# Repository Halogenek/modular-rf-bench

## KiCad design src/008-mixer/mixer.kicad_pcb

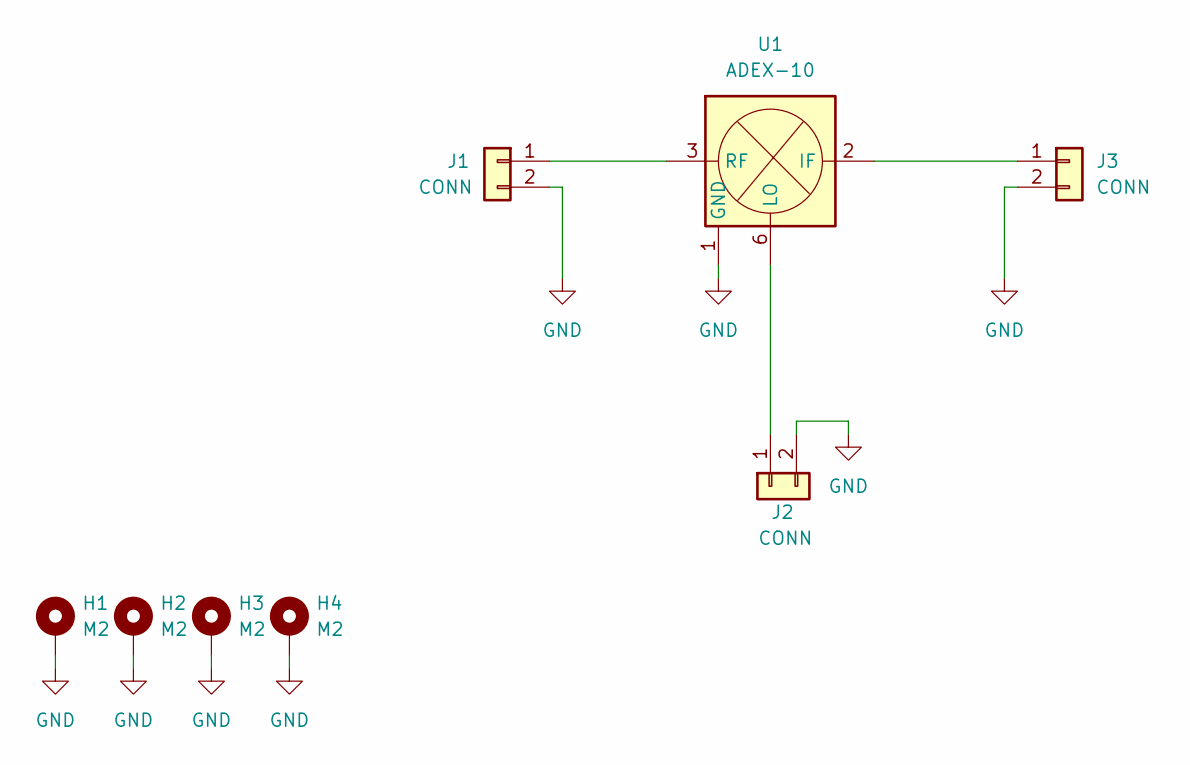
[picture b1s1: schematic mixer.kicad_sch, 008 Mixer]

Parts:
H1, H2, H3, H4: M2; M2-hole
J1, J2, J3: CONN; edge-connector
U1: ADEX-10; Mini-Circuits_CD542_LandPatternPL-052

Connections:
GND: H1.1, H2.1, H3.1, H4.1, J1.2, J2.2, J3.2, U1.1 (GND), U1.4 (GND), U1.5 (GND)
unnamed: J1.1, U1.3 (RF)
unnamed: J2.1, U1.6 (LO)
unnamed: J3.1, U1.2 (IF)

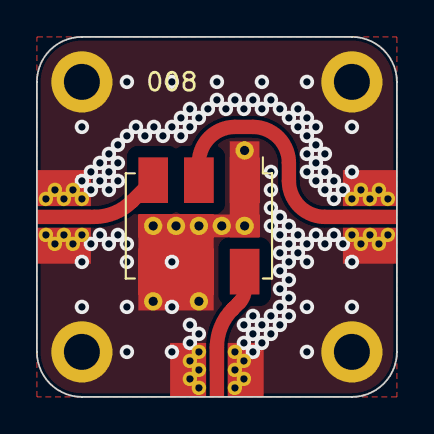
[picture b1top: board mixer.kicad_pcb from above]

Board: 2 copper layers, 20.0 x 20.0 mm, 8 parts (0 on the bottom side), 4 nets.

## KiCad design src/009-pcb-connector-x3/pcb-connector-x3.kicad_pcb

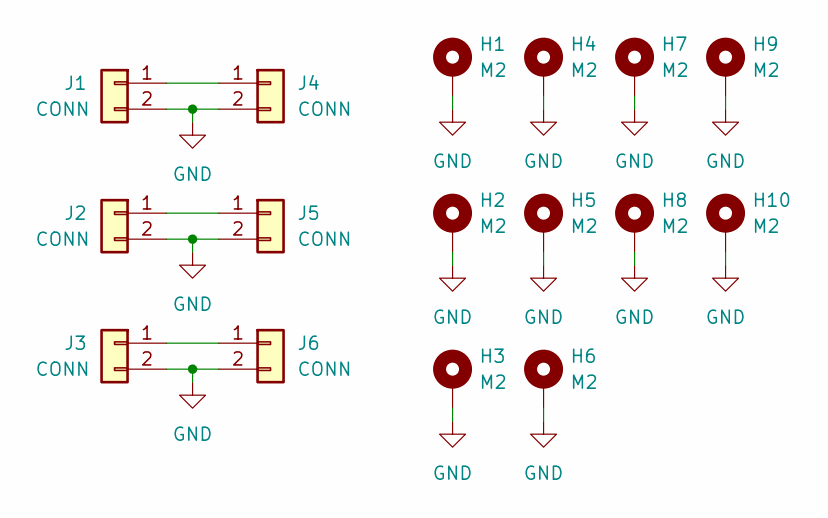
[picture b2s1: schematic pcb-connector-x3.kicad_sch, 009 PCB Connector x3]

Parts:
H1, H2, H3, H4, H5, H6, H7, H8, H9, H10: M2; M2-hole
J1, J2, J3, J4, J5, J6: CONN; edge-connector

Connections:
GND: H1.1, H2.1, H3.1, H4.1, H5.1, H6.1, H7.1, H8.1, H9.1, H10.1, J1.2, J2.2, J3.2, J4.2, J5.2, J6.2
unnamed: J1.1, J4.1
unnamed: J2.1, J5.1
unnamed: J3.1, J6.1

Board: 2 copper layers, 16 parts (0 on the bottom side), 4 nets, no tracks yet.

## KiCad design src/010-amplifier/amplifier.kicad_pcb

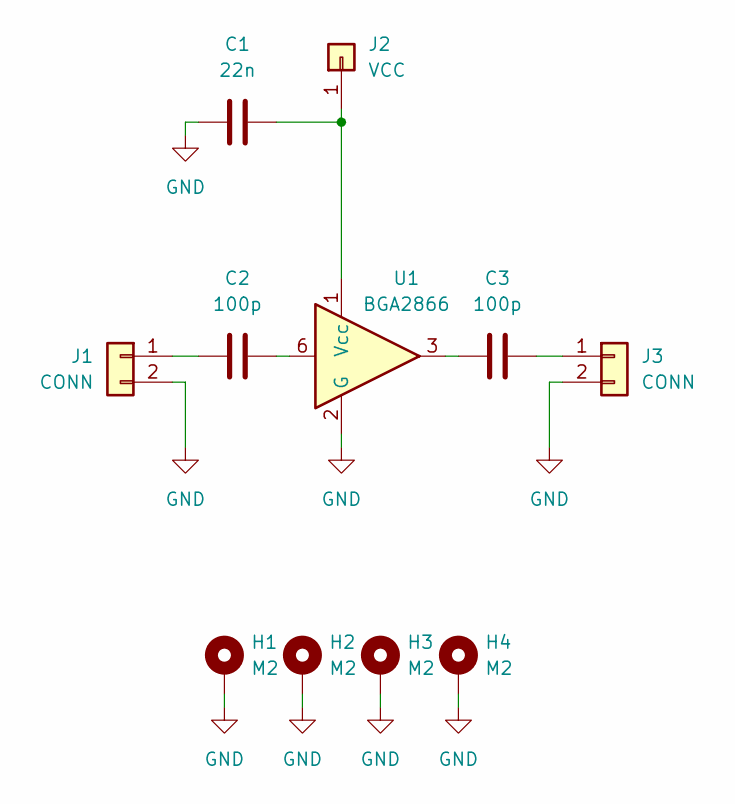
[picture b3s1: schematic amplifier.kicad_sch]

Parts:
C1: 22n; C_0603_1608Metric
C2, C3: 100p; C_0603_1608Metric
H1, H2, H3, H4: M2; M2-hole
J1, J3: CONN; edge-connector
J2: VCC; SolderWire-0.25sqmm_1x01_D0.65mm_OD1.7mm
U1: BGA2866; SOT-363_SC-70-6

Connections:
GND: C1.1, H1.1, H2.1, H3.1, H4.1, J1.2, J3.2, U1.2 (G), U1.4 (G), U1.5 (G)
unnamed: C1.2, J2.1, U1.1 (Vcc)
unnamed: C2.1, J1.1
unnamed: C2.2, U1.6
unnamed: C3.1, U1.3
unnamed: C3.2, J3.1

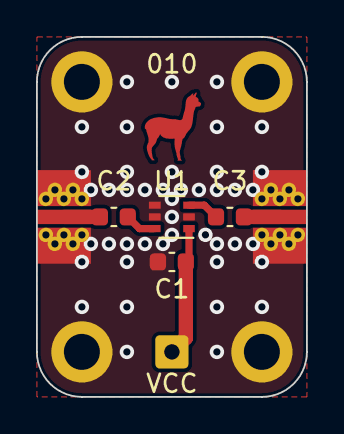
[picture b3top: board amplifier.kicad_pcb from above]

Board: 2 copper layers, 15.0 x 20.0 mm, 11 parts (0 on the bottom side), 6 nets.

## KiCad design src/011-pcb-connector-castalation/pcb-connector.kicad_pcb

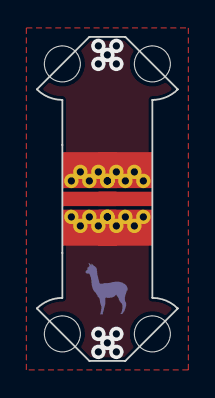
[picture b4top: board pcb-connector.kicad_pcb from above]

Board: 2 copper layers, 7.8 x 18.0 mm, 6 parts (0 on the bottom side), 2 nets, no tracks yet.

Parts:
H1, H2, H3, H4: M2; M2-hole
J1, J2: CONN; edge-connector

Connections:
GND: J1.2, J2.2
unnamed: J1.1, J2.1

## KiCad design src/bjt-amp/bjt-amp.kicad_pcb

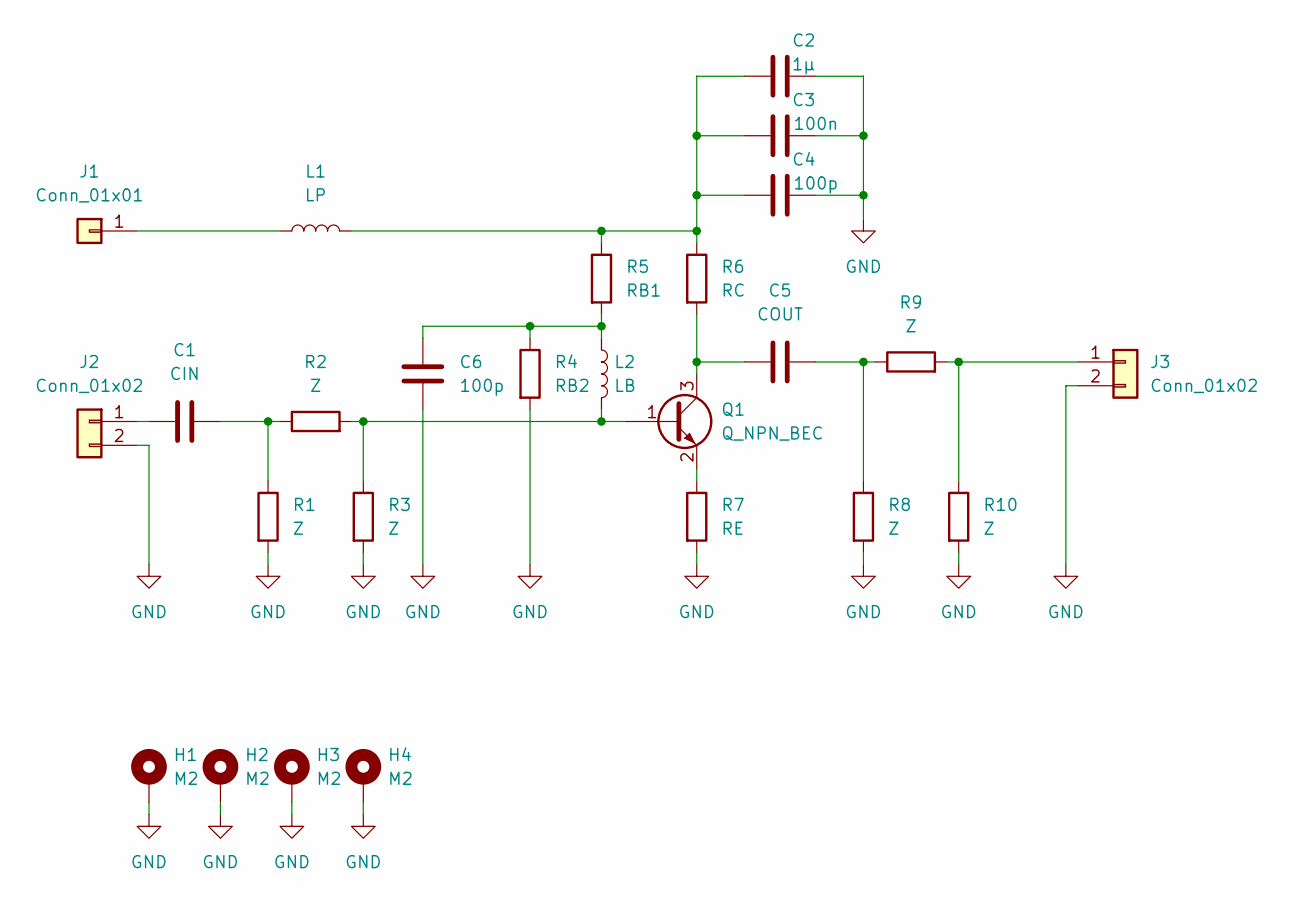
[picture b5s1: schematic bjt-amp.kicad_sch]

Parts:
C1: CIN; C_0603_1608Metric
C2: 1µ; C_0603_1608Metric
C3: 100n; C_0603_1608Metric
C4, C6: 100p; C_0603_1608Metric
C5: COUT; C_0603_1608Metric
H1, H2, H3, H4: M2; M2-hole
J1: Conn_01x01; SolderWire-0.25sqmm_1x01_D0.65mm_OD1.7mm
J2, J3: Conn_01x02; edge-connector
L1: LP; L_0603_1608Metric
L2: LB; L_0603_1608Metric
Q1: Q_NPN_BEC; SOT-23
R1, R2, R3, R8, R9, R10: Z; R_0603_1608Metric
R4: RB2; R_0603_1608Metric
R5: RB1; R_0603_1608Metric
R6: RC; R_0603_1608Metric
R7: RE; R_0603_1608Metric

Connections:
GND: C2.2, C3.2, C4.2, C6.1, H1.1, H2.1, H3.1, H4.1, J2.2, J3.2, R1.2, R3.2, R4.2, R7.2, R8.2, R10.2
unnamed: C1.1, J2.1
unnamed: C1.2, R1.1, R2.1
unnamed: C2.1, C3.1, C4.1, L1.2, R5.1, R6.1
unnamed: C5.1, Q1.3 (C), R6.2
unnamed: C5.2, R8.1, R9.1
unnamed: C6.2, L2.1, R4.1, R5.2
unnamed: J1.1, L1.1
unnamed: J3.1, R9.2, R10.1
unnamed: L2.2, Q1.1 (B), R2.2, R3.1
unnamed: Q1.2 (E), R7.1

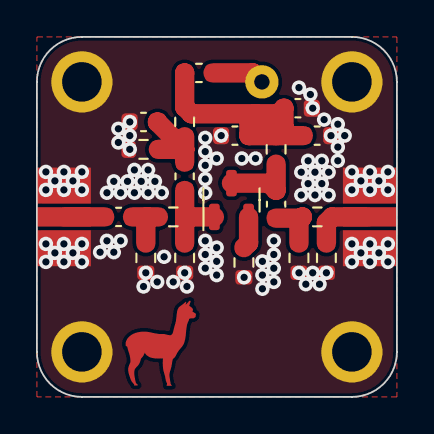
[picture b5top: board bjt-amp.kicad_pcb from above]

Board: 2 copper layers, 20.0 x 20.0 mm, 26 parts (0 on the bottom side), 11 nets.
